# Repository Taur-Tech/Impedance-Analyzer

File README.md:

# Impedance-Analyzer
HW and Software sources for an impedance analyzer module featuring Analog Devices AD5933

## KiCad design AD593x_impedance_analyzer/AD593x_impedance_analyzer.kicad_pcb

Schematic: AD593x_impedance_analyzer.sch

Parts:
C1, C2, C5: 1u; C_0805_2012Metric_Pad1.15x1.40mm_HandSolder
C3: 47n; C_0805_2012Metric_Pad1.15x1.40mm_HandSolder
C4, C6: 0.1u; C_0805_2012Metric_Pad1.15x1.40mm_HandSolder
J1, J2: Conn_01x05; PinHeader_1x05_P2.54mm_Vertical
R1, R2: 4k7; R_0805_2012Metric_Pad1.15x1.40mm_HandSolder
R3, R6: 4.7k; R_0805_2012Metric_Pad1.15x1.40mm_HandSolder
R4, R7: 20k; R_0805_2012Metric_Pad1.15x1.40mm_HandSolder
R5, R11: 0R; R_0805_2012Metric_Pad1.15x1.40mm_HandSolder
R8: 200; R_0805_2012Metric_Pad1.15x1.40mm_HandSolder
R9: 100; R_0805_2012Metric_Pad1.15x1.40mm_HandSolder
R10: 100k; R_0805_2012Metric_Pad1.15x1.40mm_HandSolder
U1: TLE2426xD; SOIC-8_3.9x4.9mm_P1.27mm
U2: AD8620; SOIC-8_3.9x4.9mm_P1.27mm
U3: AD5933; SSOP-16_5.3x6.2mm_P0.65mm
U4: TS5A3160DBV; SOT-23-6
X1: ECS-TXO-5032-160-TR; Oscillator_SMD_Fordahl_DFAS15-4Pin_5.0x3.2mm_HandSoldering

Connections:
+3V3: C6.1, J2.1, R1.1, R2.1, U3.9, X1.4
+5V: C4.1, C5.1, J1.1, U1.3, U2.8 (V+), U3.10, U3.11, U4.5 (V+)
CLK: J2.2, R5.1
DUT+: J1.3, U2.1, U2.2 (-)
DUT-: J1.4, R11.1
GND: C6.2, J2.5, U3.12, X1.2
GNDA: C1.2, C2.2, C4.2, C5.2, J1.5, U1.2, U2.4 (V-), U3.13, U3.14, U4.2 (GND)
unnamed: C1.1, U1.8
unnamed: C2.1, R3.1, R6.1, U1.1
unnamed: C3.1, R3.2, U2.3 (+)
unnamed: C3.2, U3.6
unnamed: R4.1, R7.2, U3.5
unnamed: R4.2, U3.4
unnamed: R5.2, U3.8, X1.3
unnamed: R6.2, U2.5 (+)
unnamed: R7.1, R8.2, U2.7, U4.4
unnamed: R9.2, U4.3
unnamed: R10.1, U4.1
unnamed: R8.1, R9.1, R10.2, R11.2, U2.6 (-)
RANGE_SW: J1.2, U4.6
SCL: J2.3, R2.2, U3.16
SDA: J2.4, R1.2, U3.15

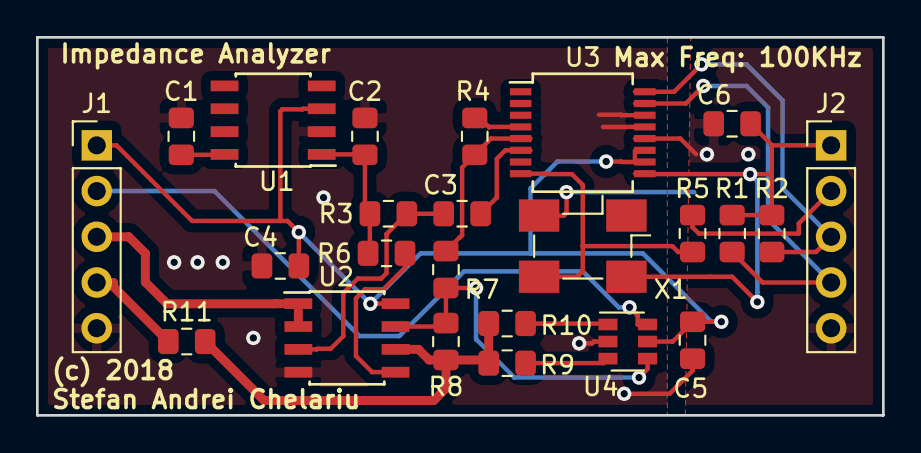
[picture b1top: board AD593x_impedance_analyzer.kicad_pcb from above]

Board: 2 copper layers, 47.0 x 21.0 mm, 24 parts (0 on the bottom side), 22 nets.

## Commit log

2018-12-02 rev 2 hardware design

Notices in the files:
AD593x_impedance_analyzer/AD593x_impedance_analyzer.kicad_pcb:
(c) 2018
(c) 2018 Stefan Andrei Chelariu
